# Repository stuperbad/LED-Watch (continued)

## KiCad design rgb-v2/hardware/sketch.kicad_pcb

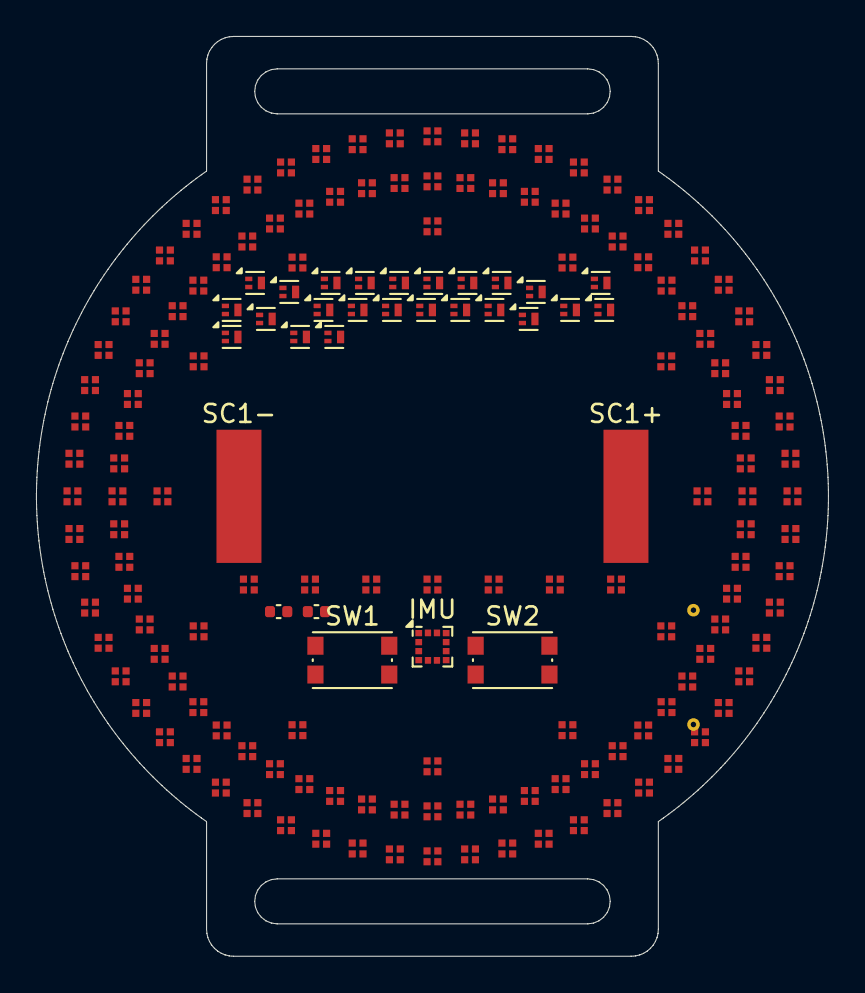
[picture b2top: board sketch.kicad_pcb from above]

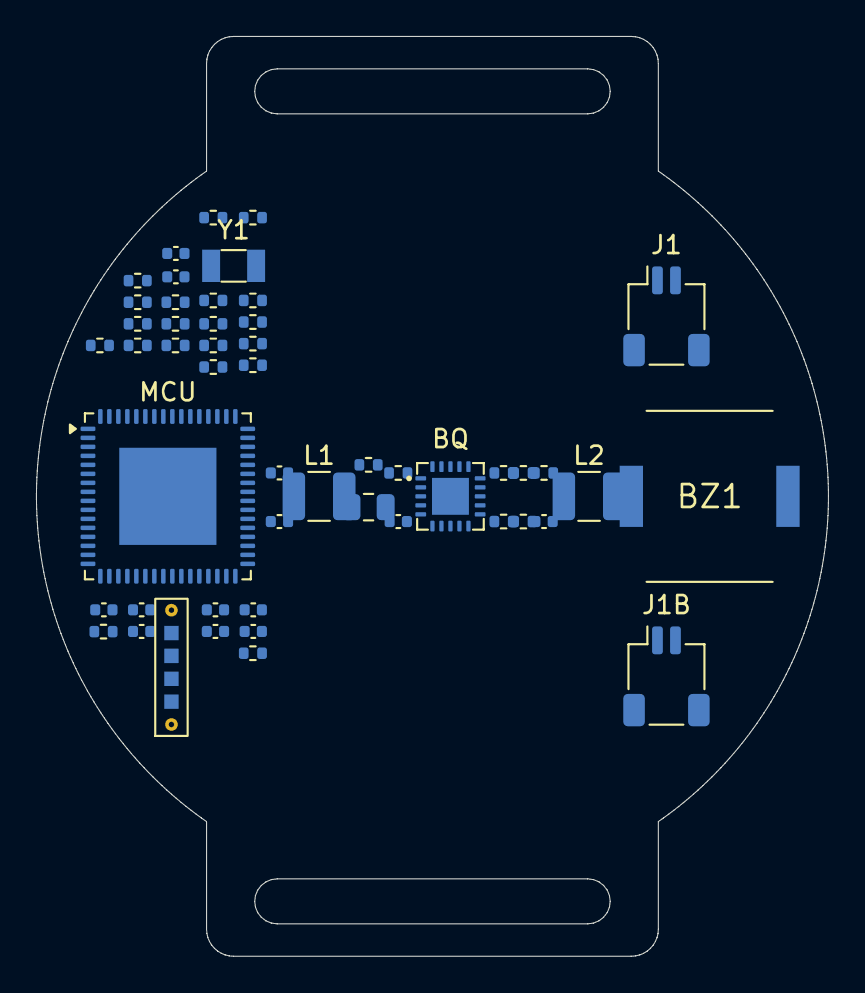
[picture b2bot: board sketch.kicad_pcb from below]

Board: 4 copper layers, 44.0 x 51.1 mm, 220 parts (50 on the bottom side), 40 nets, no tracks yet.

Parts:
BQ: BQ25570; BQ25570RGR_VQFN-20_3.5x3.5mm_P0.5mm_EP2.05mm
BZ1: PKMCS0909E4000-R1; Piezo_Murata_PKMCS0909E4000-R1_9x9mm
C20, C21: 18p; C_0402_1005Metric
C30, C31: 100n; C_0402_1005Metric
C50, C52: 4u7; C_0402_1005Metric
C51, C53: 10n; C_0402_1005Metric
C54: 22u; C_0805_2012Metric
CM1, CM2, CM3, CM4, CM5, CM6, CM7: 100n; C_0402_1005Metric
IMU: LIS2DW12; LGA-12_2x2mm_P0.5mm
IND1, IND2, IND3, IND4, IND5, IND6, IND7: NCD0808RGB1 / MHPA0808RGBDT; RGB0808_CommonAnode
J1, J1B: LiPo; JST_SH_SM02B-SRSS-TB_1x02-1MP_P1.00mm_Horizontal
J2: UPDI pogo; UPDI_Pogo_1x4_P1.27mm_2Guide
L1: 22uH; L_1210_3225Metric
L2: 10uH; L_1210_3225Metric
MCU: AVR128DB64-I/MR; VQFN-64-1EP_9x9mm_P0.5mm_EP5.4x5.4mm
Q1, Q2, Q3, Q4, Q5, Q6, Q7, Q8, Q9, Q10, Q11, Q12, Q13, Q14, Q15, Q16, Q17, Q18, Q19, Q20, Q21, Q22, Q23, Q24: DMP21D0UFB4; Diodes_DFN1006-3
R20, R21: 10k; R_0402_1005Metric
R50, R53, R55: 6.49M; R_0402_1005Metric
R51: 5.11M; R_0402_1005Metric
R52: 1.47M; R_0402_1005Metric
R54, R56: 3.74M; R_0402_1005Metric
RC1, RC2, RC3, RC4, RC5, RC6, RC7, RC8, RC9, RC10, RC11, RC12, RC13, RC14, RC15, RC16, RC17, RC18: R; R_0402_1005Metric
SC1+, SC1-: cell pad; KXOB25_cell_pad_2.5x7.4mm
SW1, SW2: SW; SW_Push_1P1T_NO_CK_KMR2
U2, U3, U4, U5, U6, U7, U8, U9, U10, U11, U12, U13, U14, U15, U16, U17, U18, U19, U20, U21, U22, U23, U24, U25, U26, U27, U28, U29, U30, U31, U32, U33, U34, U35, U36, U37, U38, U39, U40, U41, U42, U43, U44, U45, U46, U47, U48, U49, U50, U51, U52, U53, U54, U55, U56, U57, U58, U59, U60, U61, U62, U63, U64, U65, U66, U67, U68, U69, U70, U71, U72, U73, U74, U75, U76, U77, U78, U79, U80, U81, U82, U83, U84, U85, U86, U87, U88, U89, U90, U91, U92, U93, U94, U95, U96, U97, U98, U99, U100, U101, U102, U103, U104, U105, U106, U107, U108, U109, U110, U111, U112, U113, U114, U115, U116, U117, U118, U119, U120, U121, U122, U123, U124, U125, U126, U127, U128, U129, U130, U131, U132, U133: NCD0808RGB1 / MHPA0808RGBDT; RGB0808_CommonAnode
Y1: 32.768kHz; Crystal_SMD_3215-2Pin_3.2x1.5mm

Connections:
/B1: U2.4, U8.4, U14.4, U20.4, U26.4, U32.4, U38.4, U44.4, U50.4, U56.4, U62.4, U68.4, U74.4, U80.4, U86.4, U92.4, U98.4, U104.4, U110.4, U116.4, U122.4, U128.4
/B2: U3.4, U9.4, U15.4, U21.4, U27.4, U33.4, U39.4, U45.4, U51.4, U57.4, U63.4, U69.4, U75.4, U81.4, U87.4, U93.4, U99.4, U105.4, U111.4, U117.4, U123.4, U129.4
/B3: U4.4, U10.4, U16.4, U22.4, U28.4, U34.4, U40.4, U46.4, U52.4, U58.4, U64.4, U70.4, U76.4, U82.4, U88.4, U94.4, U100.4, U106.4, U112.4, U118.4, U124.4, U130.4
/B4: U5.4, U11.4, U17.4, U23.4, U29.4, U35.4, U41.4, U47.4, U53.4, U59.4, U65.4, U71.4, U77.4, U83.4, U89.4, U95.4, U101.4, U107.4, U113.4, U119.4, U125.4, U131.4
/B5: U6.4, U12.4, U18.4, U24.4, U30.4, U36.4, U42.4, U48.4, U54.4, U60.4, U66.4, U72.4, U78.4, U84.4, U90.4, U96.4, U102.4, U108.4, U114.4, U120.4, U126.4, U132.4
/B6: U7.4, U13.4, U19.4, U25.4, U31.4, U37.4, U43.4, U49.4, U55.4, U61.4, U67.4, U73.4, U79.4, U85.4, U91.4, U97.4, U103.4, U109.4, U115.4, U121.4, U127.4, U133.4
/G1: U2.3, U8.3, U14.3, U20.3, U26.3, U32.3, U38.3, U44.3, U50.3, U56.3, U62.3, U68.3, U74.3, U80.3, U86.3, U92.3, U98.3, U104.3, U110.3, U116.3, U122.3, U128.3
/G2: U3.3, U9.3, U15.3, U21.3, U27.3, U33.3, U39.3, U45.3, U51.3, U57.3, U63.3, U69.3, U75.3, U81.3, U87.3, U93.3, U99.3, U105.3, U111.3, U117.3, U123.3, U129.3
/G3: U4.3, U10.3, U16.3, U22.3, U28.3, U34.3, U40.3, U46.3, U52.3, U58.3, U64.3, U70.3, U76.3, U82.3, U88.3, U94.3, U100.3, U106.3, U112.3, U118.3, U124.3, U130.3
/G4: U5.3, U11.3, U17.3, U23.3, U29.3, U35.3, U41.3, U47.3, U53.3, U59.3, U65.3, U71.3, U77.3, U83.3, U89.3, U95.3, U101.3, U107.3, U113.3, U119.3, U125.3, U131.3
/G5: U6.3, U12.3, U18.3, U24.3, U30.3, U36.3, U42.3, U48.3, U54.3, U60.3, U66.3, U72.3, U78.3, U84.3, U90.3, U96.3, U102.3, U108.3, U114.3, U120.3, U126.3, U132.3
/G6: U7.3, U13.3, U19.3, U25.3, U31.3, U37.3, U43.3, U49.3, U55.3, U61.3, U67.3, U73.3, U79.3, U85.3, U91.3, U97.3, U103.3, U109.3, U115.3, U121.3, U127.3, U133.3
/Hour1: U2.1, U3.1, U4.1, U5.1, U6.1, U7.1
/Hour2: U8.1, U9.1, U10.1, U11.1, U12.1, U13.1
/Minute1: U14.1, U15.1, U16.1, U17.1, U18.1, U19.1
/Minute2: U20.1, U21.1, U22.1, U23.1, U24.1, U25.1
/Minute3: U26.1, U27.1, U28.1, U29.1, U30.1, U31.1
/Minute4: U32.1, U33.1, U34.1, U35.1, U36.1, U37.1
/Minute5: U38.1, U39.1, U40.1, U41.1, U42.1, U43.1
/Minute6: U44.1, U45.1, U46.1, U47.1, U48.1, U49.1
/Minute7: U50.1, U51.1, U52.1, U53.1, U54.1, U55.1
/Minute8: U56.1, U57.1, U58.1, U59.1, U60.1, U61.1
/Minute9: U62.1, U63.1, U64.1, U65.1, U66.1, U67.1
/Minute10: U68.1, U69.1, U70.1, U71.1, U72.1, U73.1
/R1: U2.2, U8.2, U14.2, U20.2, U26.2, U32.2, U38.2, U44.2, U50.2, U56.2, U62.2, U68.2, U74.2, U80.2, U86.2, U92.2, U98.2, U104.2, U110.2, U116.2, U122.2, U128.2
/R2: U3.2, U9.2, U15.2, U21.2, U27.2, U33.2, U39.2, U45.2, U51.2, U57.2, U63.2, U69.2, U75.2, U81.2, U87.2, U93.2, U99.2, U105.2, U111.2, U117.2, U123.2, U129.2
/R3: U4.2, U10.2, U16.2, U22.2, U28.2, U34.2, U40.2, U46.2, U52.2, U58.2, U64.2, U70.2, U76.2, U82.2, U88.2, U94.2, U100.2, U106.2, U112.2, U118.2, U124.2, U130.2
/R4: U5.2, U11.2, U17.2, U23.2, U29.2, U35.2, U41.2, U47.2, U53.2, U59.2, U65.2, U71.2, U77.2, U83.2, U89.2, U95.2, U101.2, U107.2, U113.2, U119.2, U125.2, U131.2
/R5: U6.2, U12.2, U18.2, U24.2, U30.2, U36.2, U42.2, U48.2, U54.2, U60.2, U66.2, U72.2, U78.2, U84.2, U90.2, U96.2, U102.2, U108.2, U114.2, U120.2, U126.2, U132.2
/R6: U7.2, U13.2, U19.2, U25.2, U31.2, U37.2, U43.2, U49.2, U55.2, U61.2, U67.2, U73.2, U79.2, U85.2, U91.2, U97.2, U103.2, U109.2, U115.2, U121.2, U127.2, U133.2
/Second1: U74.1, U75.1, U76.1, U77.1, U78.1, U79.1
/Second2: U80.1, U81.1, U82.1, U83.1, U84.1, U85.1
/Second3: U86.1, U87.1, U88.1, U89.1, U90.1, U91.1
/Second4: U92.1, U93.1, U94.1, U95.1, U96.1, U97.1
/Second5: U98.1, U99.1, U100.1, U101.1, U102.1, U103.1
/Second6: U104.1, U105.1, U106.1, U107.1, U108.1, U109.1
/Second7: U110.1, U111.1, U112.1, U113.1, U114.1, U115.1
/Second8: U116.1, U117.1, U118.1, U119.1, U120.1, U121.1
/Second9: U122.1, U123.1, U124.1, U125.1, U126.1, U127.1
/Second10: U128.1, U129.1, U130.1, U131.1, U132.1, U133.1
